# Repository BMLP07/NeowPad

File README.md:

<div align="center">
  
# NeowPad
Macropad designed for productivity with customizable encoder and keys

</div>

## Description
A medium-sized 15-key macropad with a rotatory encoder. The encoder and every key can be customized as wished on the firmware powered by a XIAO RP2040

## Features
- Every key can be customized as well as the encoder
- Main functions are single-input, multiple-input and macros.
  
**Future plans:**
- Not a single layout but multiple for different task (work, games, ...)
- Key-pressed combinations for more functionality

## BOM
- 1x Case (Top & Bottom)
- 1x Unsoldered Seeed XIAO RP2040
- 15x MX-Style switches
- 15x White blank DSA keycaps
- 15x Through-hole 1N4148 Diodes
- 1x EC11 Rotary encoders
- 4x M3x16mm screws
- 4x M3x5mx4mm heatset inserts

## Design
| **Schematic** |
| :---: |
|  |
| **PCB** |
|  |
| **CAD** |
|  |

## File descriptions

- **CAD**: Contains .stp/.step files and .f3b files.
- **Firmware**: Contains KMK python file.
- **PCB**: Contains gerber.zip (for production), PCB schematic and layout.
- **Production**: All files necessary for the production of the macropad.

## Comments
It has been a lovely journey learning how to design a PCB in KiCAD, the case in CAD programs and learning how to code a firmware for a macropad. <br> Thanks for the opportunity and eager to learn more about hardware, software and more!
<div align="center">

</div>

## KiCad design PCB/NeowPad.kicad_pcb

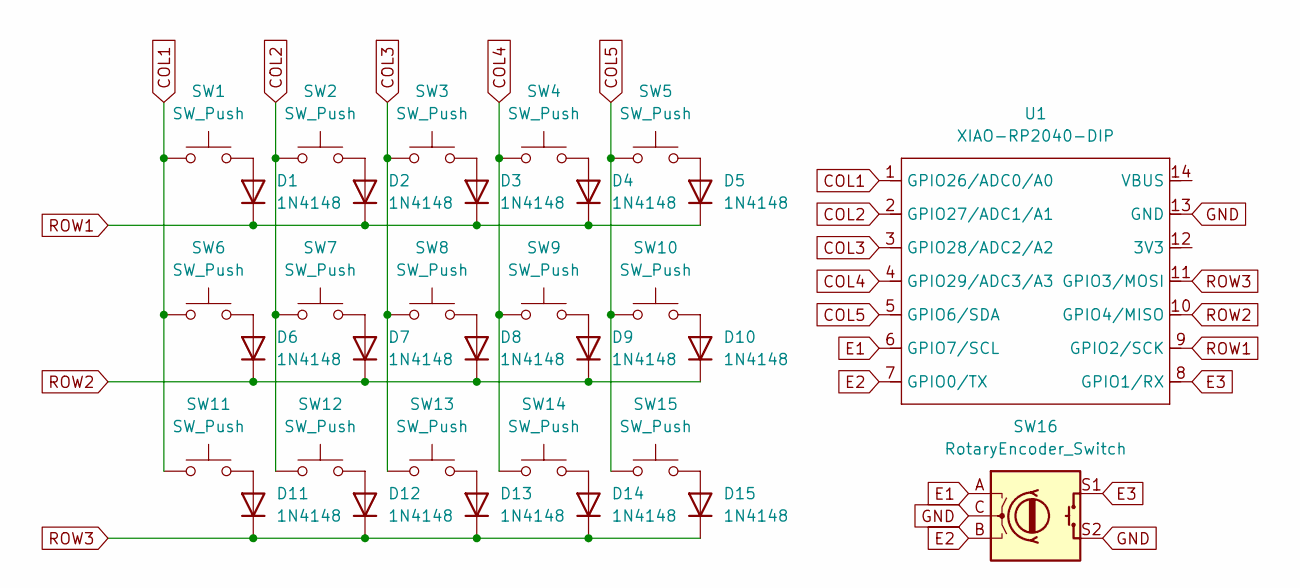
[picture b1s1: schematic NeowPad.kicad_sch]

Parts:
D1, D2, D3, D4, D5, D6, D7, D8, D9, D10, D11, D12, D13, D14, D15: 1N4148; D_DO-35_SOD27_P7.62mm_Horizontal
SW1, SW2, SW3, SW4, SW5, SW6, SW7, SW8, SW9, SW10, SW11, SW12, SW13, SW14, SW15: SW_Push; SW_Cherry_MX_1.00u_PCB
SW16: RotaryEncoder_Switch; RotaryEncoder_Alps_EC11E-Switch_Vertical_H20mm
U1: XIAO-RP2040-DIP

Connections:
COL1: SW1.1, SW6.1, SW11.1, U1.1 (GPIO26/ADC0/A0)
COL2: SW2.1, SW7.1, SW12.1, U1.2 (GPIO27/ADC1/A1)
COL3: SW3.1, SW8.1, SW13.1, U1.3 (GPIO28/ADC2/A2)
COL4: SW4.1, SW9.1, SW14.1, U1.4 (GPIO29/ADC3/A3)
COL5: SW5.1, SW10.1, SW15.1, U1.5 (GPIO6/SDA)
E1: SW16.A, U1.6 (GPIO7/SCL)
E2: SW16.B, U1.7 (GPIO0/TX)
E3: SW16.S1, U1.8 (GPIO1/RX)
GND: SW16.C, SW16.S2, U1.13 (GND)
unnamed: D1.2 (A), SW1.2
unnamed: D2.2 (A), SW2.2
unnamed: D3.2 (A), SW3.2
unnamed: D4.2 (A), SW4.2
unnamed: D5.2 (A), SW5.2
unnamed: D6.2 (A), SW6.2
unnamed: D7.2 (A), SW7.2
unnamed: D8.2 (A), SW8.2
unnamed: D9.2 (A), SW9.2
unnamed: D10.2 (A), SW10.2
unnamed: D11.2 (A), SW11.2
unnamed: D12.2 (A), SW12.2
unnamed: D13.2 (A), SW13.2
unnamed: D14.2 (A), SW14.2
unnamed: D15.2 (A), SW15.2
ROW1: D1.1 (K), D2.1 (K), D3.1 (K), D4.1 (K), D5.1 (K), U1.9 (GPIO2/SCK)
ROW2: D6.1 (K), D7.1 (K), D8.1 (K), D9.1 (K), D10.1 (K), U1.10 (GPIO4/MISO)
ROW3: D11.1 (K), D12.1 (K), D13.1 (K), D14.1 (K), D15.1 (K), U1.11 (GPIO3/MOSI)

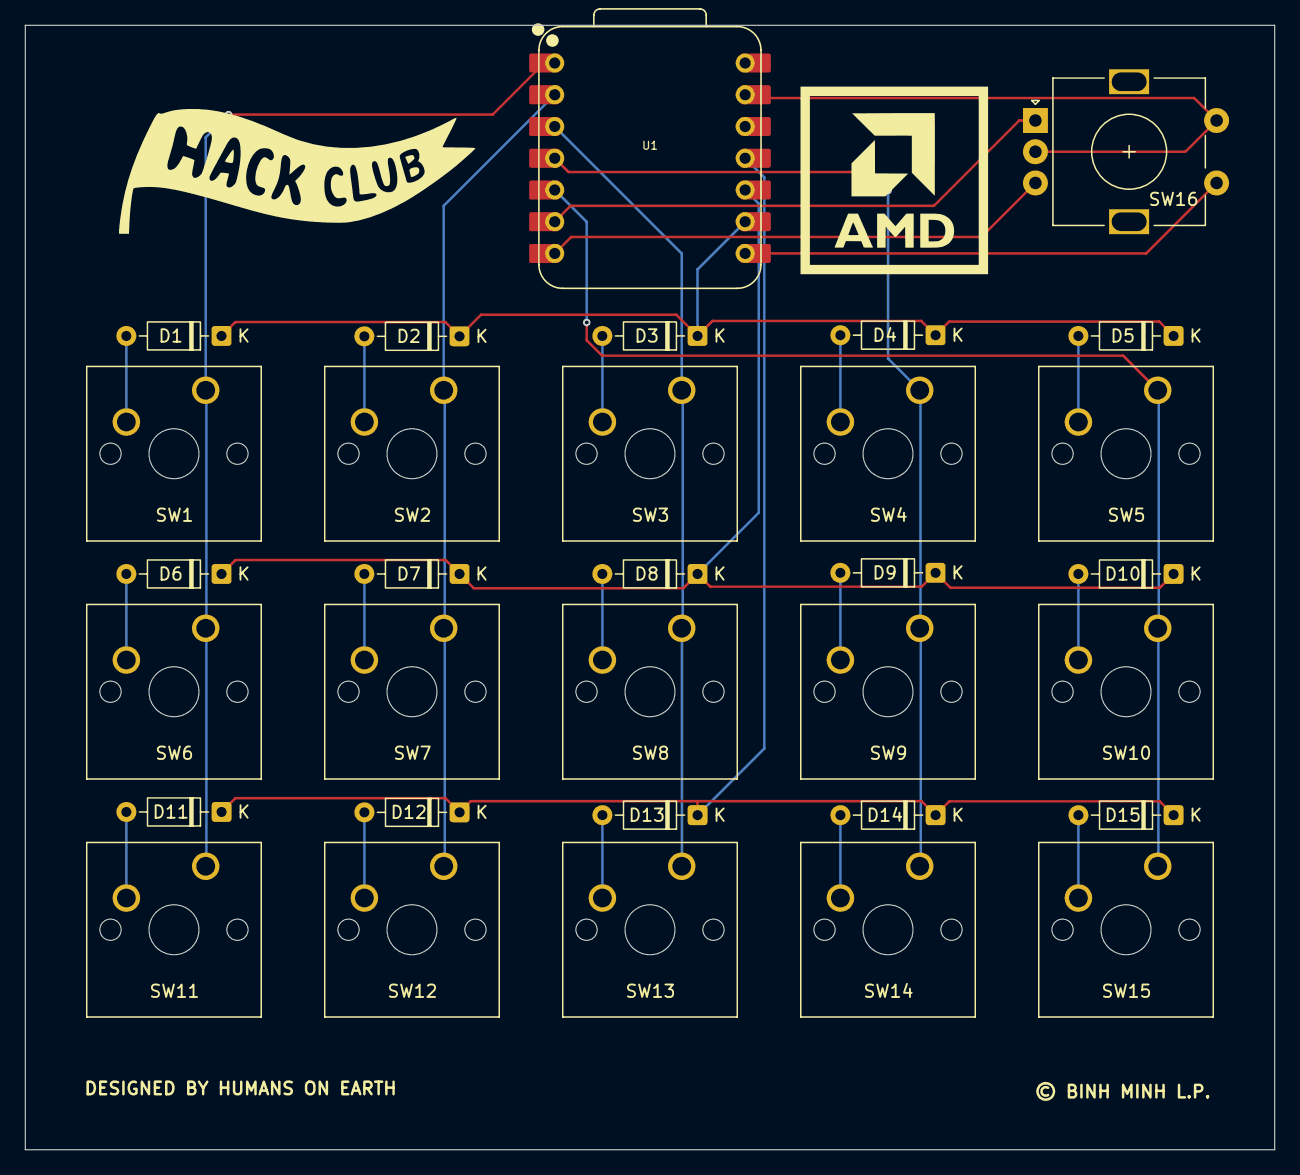
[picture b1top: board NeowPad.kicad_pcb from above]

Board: 2 copper layers, 100.0 x 90.0 mm, 32 parts (0 on the bottom side), 27 nets.

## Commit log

2026-03-31 Enhance README with BOM and design details
    Added a Bill of Materials (BOM) and design section to the README.
2026-03-31 Update image links in README design section
2026-03-31 Add comments section to README
    Added comments section to share learning experiences in PCB design and firmware coding.
2026-04-01 Enhance README with project details and comments
    Expanded the README to include a detailed project description, updated section headers, and added comments about the design process.
2026-04-01 Enhance README with project details and roadmap
    Expanded project description and added key features and future roadmap.
2026-04-01 Revise README for clarity and feature expansion
    Updated the README to enhance clarity and added future plans for multiple layouts and key combinations.
2026-04-01 Enhance README with file descriptions
    Added file descriptions for CAD, Firmware, PCB, and Production sections.
2026-04-01 Refactor README.md to eliminate duplicate entries
    Removed duplicate file descriptions and cleaned up formatting.
2026-04-02 Improve formatting of design section in README
    Reformatted design section in README for better clarity.
2026-04-02 Rename Design Assembled.png to Design_Assembled.png
2026-04-02 Update image links in README for schematic and PCB
2026-04-02 Update formatting for design section in README
2026-04-02 Add visitor counter badge to README
    Added a visitor counter badge to the README.
2026-05-31 Refactor KMK Keyboard setup with media keys support
2026-06-11 Refactor keymap and row pin configuration
    Rearranged row pin order and updated keymap actions.

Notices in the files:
PCB/NeowPad.kicad_pcb:
© BINH MINH L.P.
